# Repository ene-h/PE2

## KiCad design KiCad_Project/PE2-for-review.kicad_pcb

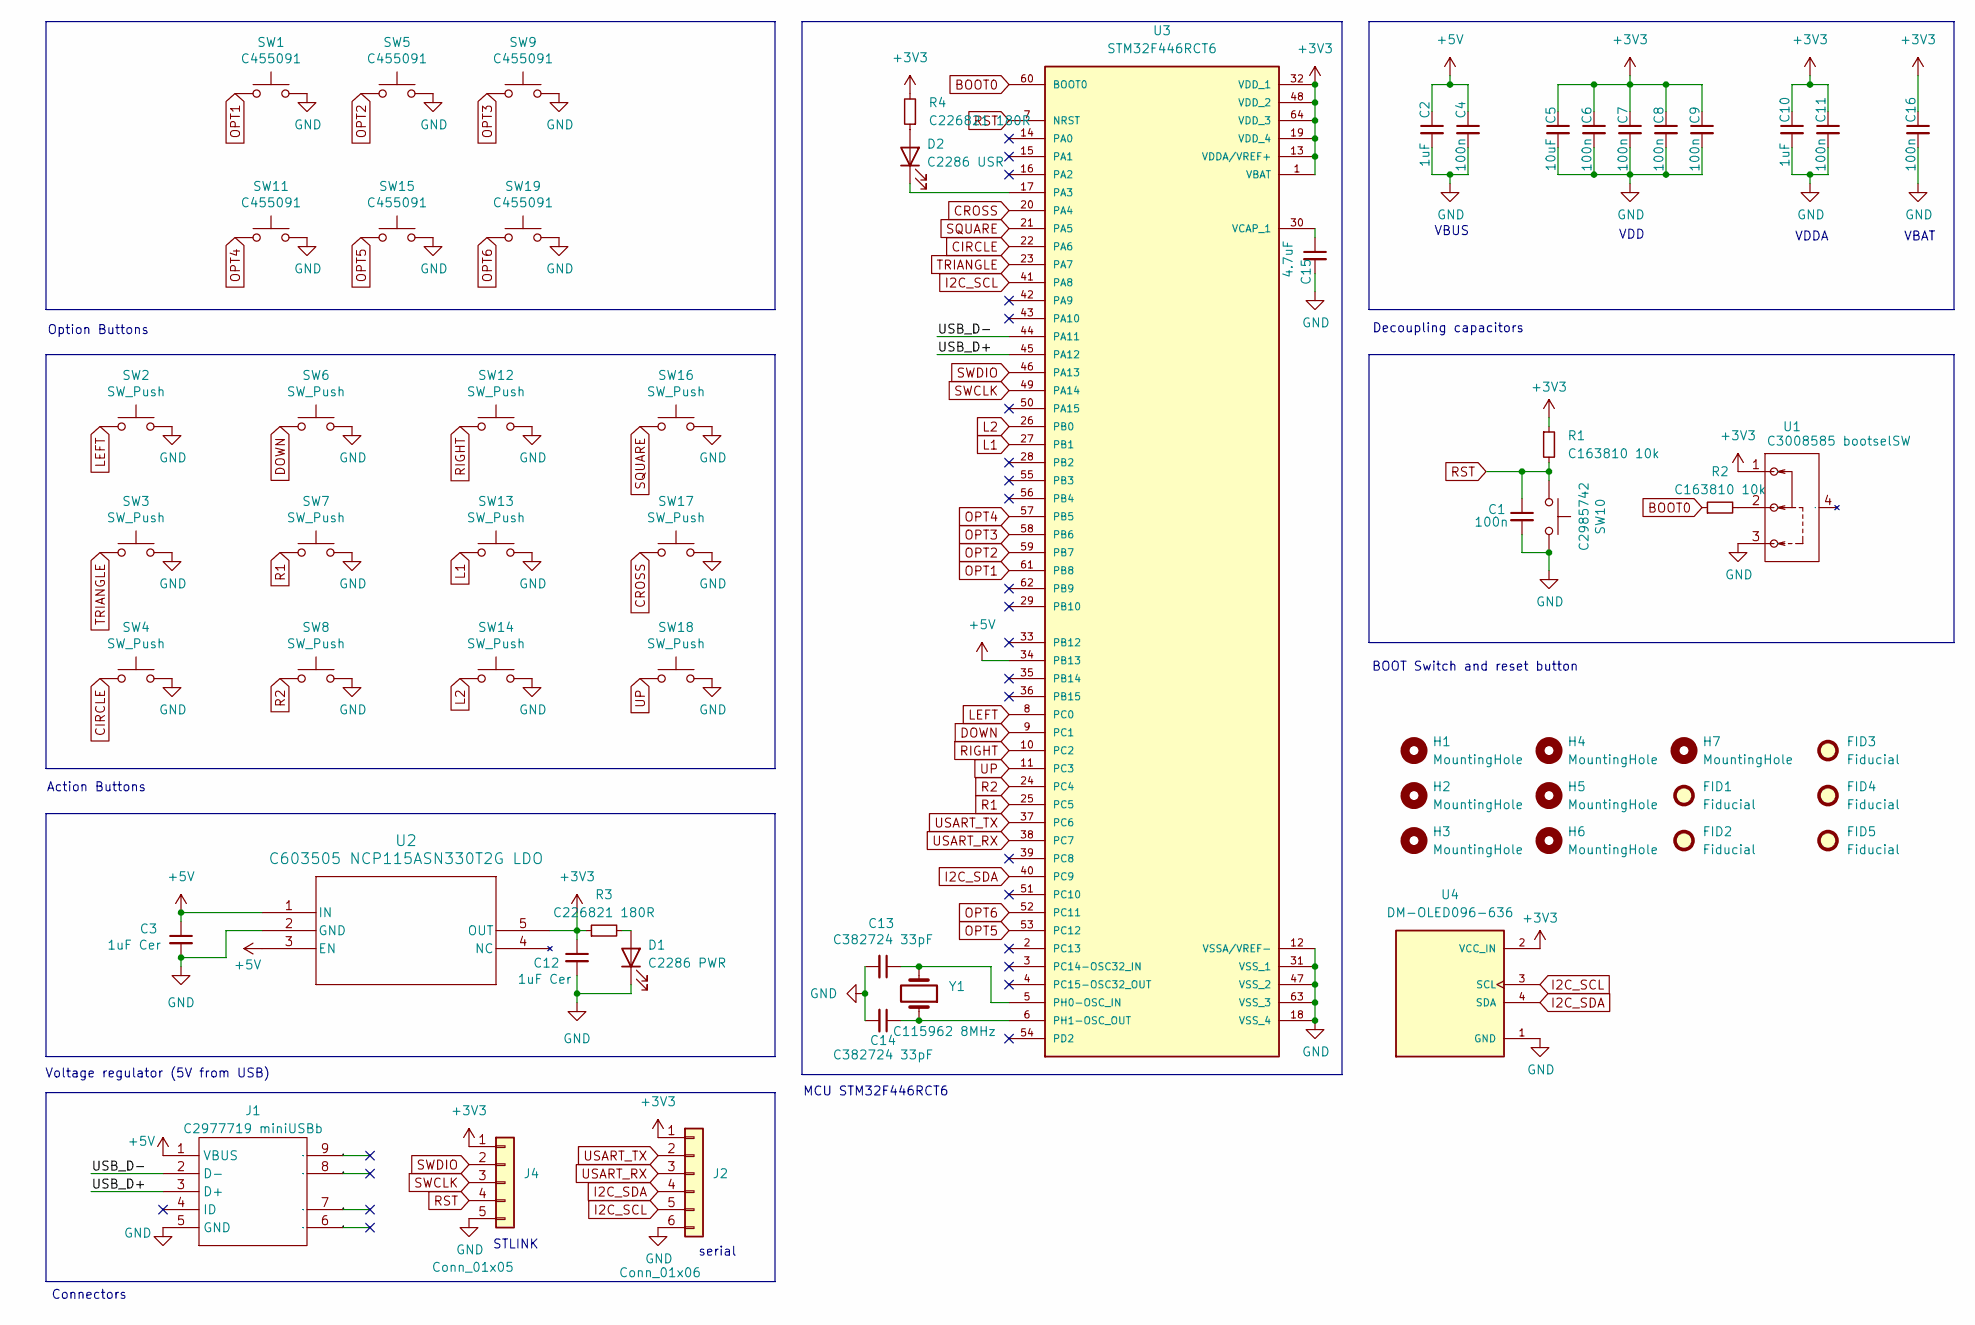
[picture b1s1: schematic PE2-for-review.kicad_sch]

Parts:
C1, C4, C6, C7, C8, C9, C11, C16: 100n; C_0402_1005Metric
C2, C10: 1uF; C_0603_1608Metric
C3, C12: 1uF Cer; C_0603_1608Metric
C5: 10uF; C_0603_1608Metric
C13, C14: C382724 33pF; C_0402_1005Metric
C15: 4.7uF; C_0603_1608Metric
D1: C2286 PWR; LED_0603_1608Metric
D2: C2286 USR; LED_0603_1608Metric
FID1, FID2, FID3: Fiducial; Fiducial_0.75mm_Mask2.25mm
FID4, FID5: Fiducial; Fiducial_0.5mm_Mask1mm
H1, H2, H3, H4, H5, H6, H7: MountingHole; MountingHole_6.3mm
J1: C2977719 miniUSBb; JLC_MINI-USB-SMD
J2: Conn_01x06; PinHeader_1x06_P2.54mm_Horizontal
J4: Conn_01x05; PinHeader_1x05_P2.54mm_Horizontal
R1, R2: C163810 10k; R_0402_1005Metric
R3, R4: C226821 180R; R_0402_1005Metric
SW1, SW5, SW9, SW11, SW15, SW19: C455091; SW_PUSH_6mm_H5mm
SW2, SW3, SW4, SW6, SW7, SW8, SW12, SW13, SW14, SW16, SW17, SW18: SW_Push; Kailh_socket_PG1350_optional
SW10: C2985742; JLC_TactSW_Low-profile
U1: C3008585 bootselSW; JLC_SW-SMD
U2: C603505 NCP115ASN330T2G LDO; SOT95P275X110-5N
U3: STM32F446RCT6
U4: DM-OLED096-636; MODULE_DM-OLED096-636; PARTREV 2018-09-10
Y1: C115962 8MHz; Crystal_SMD_5032-2Pin_5.0x3.2mm

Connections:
+3V3: C5.1, C6.1, C7.1, C8.1, C9.1, C10.1, C11.1, C12.1, C16.1, J2.1, J4.1, R1.1, R3.1, R4.2, U1.1, U2.5 (OUT), U3.1 (VBAT), U3.13 (VDDA/VREF+), U3.19 (VDD_4), U3.32 (VDD_1), U3.48 (VDD_2), U3.64 (VDD_3), U4.2 (VCC_IN)
+5V: C2.1, C3.1, C4.1, J1.1 (VBUS), U2.1 (IN), U2.3 (EN), U3.34 (PB13)
/UC1: J1.9 (EH)
/UC2: J1.8 (EH)
/UC3: J1.7 (EH)
/UC4: J1.6 (EH)
/USB_D+: J1.3 (D+), U3.45 (PA12)
/USB_D-: J1.2 (D-), U3.44 (PA11)
BOOT0: R2.1, U3.60 (BOOT0)
CIRCLE: SW4.1, U3.22 (PA6)
CROSS: SW17.1, U3.20 (PA4)
DOWN: SW6.1, U3.9 (PC1)
GND: C1.2, C2.2, C3.2, C4.2, C5.2, C6.2, C7.2, C8.2, C9.2, C10.2, C11.2, C12.2, C13.2, C14.2, C15.2, C16.2, D1.1 (K), J1.5 (GND), J2.6, J4.5, SW1.2, SW2.2, SW3.2, SW4.2, SW5.2, SW6.2, SW7.2, SW8.2, SW9.2, SW10.2, SW11.2, SW12.2, SW13.2, SW14.2, SW15.2, SW16.2, SW17.2, SW18.2, SW19.2, U1.3, U2.2 (GND), U3.12 (VSSA/VREF-), U3.18 (VSS_4), U3.31 (VSS_1), U3.47 (VSS_2), U3.63 (VSS_3), U4.1 (GND)
I2C_SCL: J2.5, U3.41 (PA8), U4.3 (SCL)
I2C_SDA: J2.4, U3.40 (PC9), U4.4 (SDA)
L1: SW13.1, U3.27 (PB1)
L2: SW14.1, U3.26 (PB0)
LEFT: SW2.1, U3.8 (PC0)
unnamed: D1.2 (A), R3.2
unnamed: D2.2 (A), R4.1
unnamed: D2.1 (K), U3.17 (PA3)
unnamed: R2.2, U1.2
unnamed: C13.1, U3.5 (PH0-OSC_IN), Y1.2
unnamed: C14.1, U3.6 (PH1-OSC_OUT), Y1.1
unnamed: C15.1, U3.30 (VCAP_1)
OPT1: SW1.1, U3.61 (PB8)
OPT2: SW5.1, U3.59 (PB7)
OPT3: SW9.1, U3.58 (PB6)
OPT4: SW11.1, U3.57 (PB5)
OPT5: SW15.1, U3.53 (PC12)
OPT6: SW19.1, U3.52 (PC11)
R1: SW7.1, U3.25 (PC5)
R2: SW8.1, U3.24 (PC4)
RIGHT: SW12.1, U3.10 (PC2)
RST: C1.1, J4.4, R1.2, SW10.1, U3.7 (NRST)
SQUARE: SW16.1, U3.21 (PA5)
SWCLK: J4.3, U3.49 (PA14)
SWDIO: J4.2, U3.46 (PA13)
TRIANGLE: SW3.1, U3.23 (PA7)
UP: SW18.1, U3.11 (PC3)
USART_RX: J2.3, U3.38 (PC7)
USART_TX: J2.2, U3.37 (PC6)

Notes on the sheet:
Voltage regulator (5V from USB)
MCU STM32F446RCT6
serial
BOOT Switch and reset button
STLINK
Connectors
VBAT
Decoupling capacitors
Option Buttons
VBUS
VDD
Action Buttons
VDDA

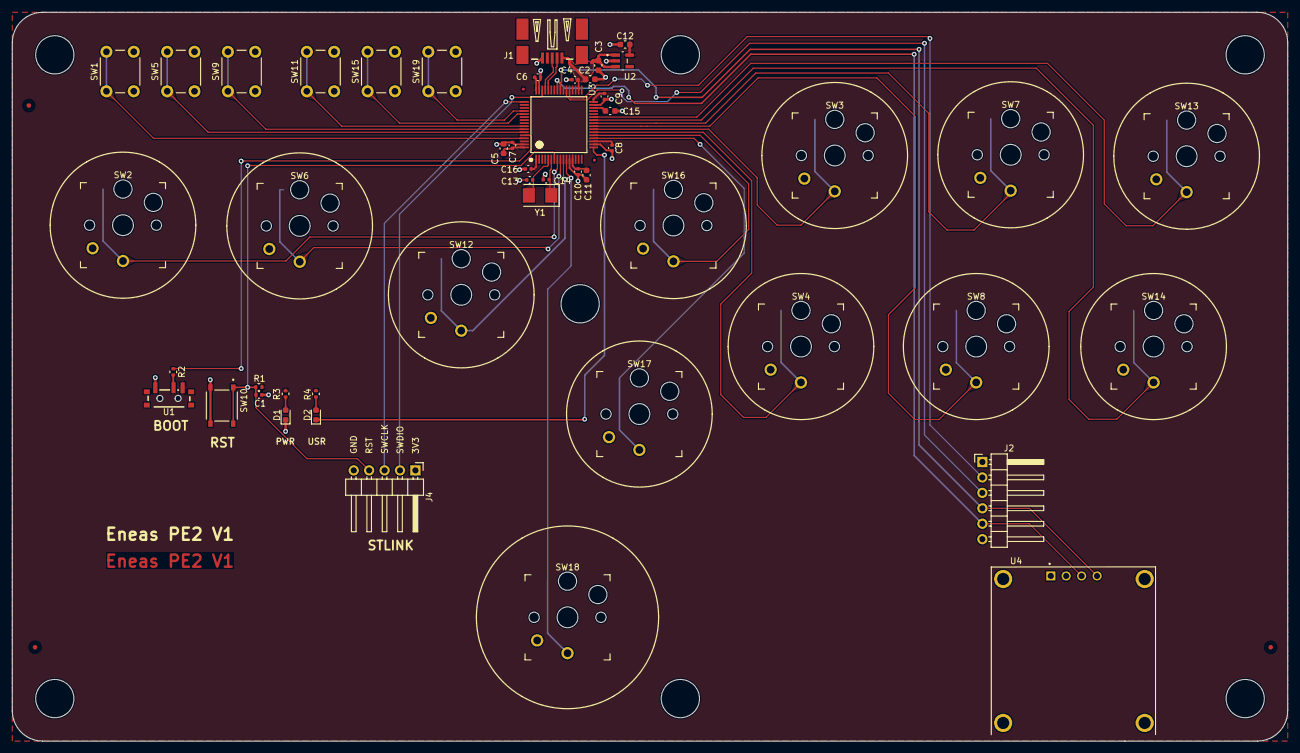
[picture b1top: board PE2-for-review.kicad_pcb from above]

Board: 2 copper layers, 210.0 x 120.0 mm, 61 parts (0 on the bottom side), 38 nets.

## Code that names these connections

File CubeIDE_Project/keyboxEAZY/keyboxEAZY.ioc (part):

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Mcu.Name=STM32F446R(C-E)Tx
Mcu.Package=LQFP64
Mcu.UserName=STM32F446RCTx
PA11.Mode=Device_Only
PA11.Signal=USB_OTG_FS_DM
PA12.Mode=Device_Only
PA12.Signal=USB_OTG_FS_DP
PA13.Signal=SYS_JTMS-SWDIO
PA3.GPIOParameters=GPIO_Label
PA3.GPIO_Label=LED
PA3.Signal=GPIO_Output
PA4.GPIOParameters=GPIO_PuPd,GPIO_Label,GPIO_Mode
PA4.GPIO_Label=LK
PA4.GPIO_Mode=GPIO_MODE_INPUT
PA4.GPIO_PuPd=GPIO_PULLUP
PA4.Signal=GPIO_Input
PA5.GPIOParameters=GPIO_PuPd,GPIO_Label,GPIO_Mode
PA5.GPIO_Label=LP
PA5.GPIO_Mode=GPIO_MODE_INPUT
PA5.GPIO_PuPd=GPIO_PULLUP
PA5.Signal=GPIO_Input
PA6.GPIOParameters=GPIO_PuPd,GPIO_Label,GPIO_Mode
PA6.GPIO_Label=MK
PA6.GPIO_Mode=GPIO_MODE_INPUT
PA6.GPIO_PuPd=GPIO_PULLUP
PA6.Signal=GPIO_Input
PA7.GPIOParameters=GPIO_PuPd,GPIO_Label,GPIO_Mode
PA7.GPIO_Label=MP
PA7.GPIO_Mode=GPIO_MODE_INPUT
PA7.GPIO_PuPd=GPIO_PULLUP
PA7.Signal=GPIO_Input
PA8.GPIOParameters=GPIO_Pu
PA8.GPIO_Pu=GPIO_PULLUP
PA8.Mode=I2C
PA8.Signal=I2C3_SCL
PB0.GPIOParameters=GPIO_PuPd,GPIO_Label
PB0.GPIO_Label=EXK
PB0.GPIO_PuPd=GPIO_PULLUP
PB0.Signal=GPIO_Input
PB1.GPIOParameters=GPIO_PuPd,GPIO_Label
PB1.GPIO_Label=EXP
PB1.GPIO_PuPd=GPIO_PULLUP
PB1.Signal=GPIO_Input
PB13.Signal=USB_OTG_HS_VBUS
PB5.GPIOParameters=GPIO_PuPd,GPIO_Label
PB5.GPIO_Label=OPT4
PB5.GPIO_PuPd=GPIO_PULLUP
PB5.Signal=GPIO_Input
PB6.GPIOParameters=GPIO_PuPd,GPIO_Label
PB6.GPIO_Label=OPT3
PB6.GPIO_PuPd=GPIO_PULLUP
PB6.Signal=GPIO_Input
PB7.GPIOParameters=GPIO_PuPd,GPIO_Label
PB7.GPIO_Label=OPT2
PB7.GPIO_PuPd=GPIO_PULLUP
PB7.Signal=GPIO_Input
PB8.GPIOParameters=GPIO_PuPd,GPIO_Label
PB8.GPIO_Label=OPT1
PB8.GPIO_PuPd=GPIO_PULLUP
PB8.Signal=GPIO_Input
PC0.GPIOParameters=GPIO_PuPd,GPIO_Label,GPIO_Mode
PC0.GPIO_Label=LEFT
PC0.GPIO_Mode=GPIO_MODE_INPUT
PC0.GPIO_PuPd=GPIO_PULLUP
PC0.Signal=GPIO_Input
PC1.GPIOParameters=GPIO_PuPd,GPIO_Label,GPIO_Mode
PC1.GPIO_Label=DOWN
PC1.GPIO_Mode=GPIO_MODE_INPUT
PC1.GPIO_PuPd=GPIO_PULLUP
PC1.Signal=GPIO_Input
PC11.GPIOParameters=GPIO_PuPd,GPIO_Label
PC11.GPIO_Label=OPT6
PC11.GPIO_PuPd=GPIO_PULLUP
PC11.Signal=GPIO_Input
PC12.GPIOParameters=GPIO_PuPd,GPIO_Label
PC12.GPIO_Label=OPT5
PC12.GPIO_PuPd=GPIO_PULLUP
PC12.Signal=GPIO_Input
PC2.GPIOParameters=GPIO_PuPd,GPIO_Label,GPIO_Mode
PC2.GPIO_Label=RIGHT
PC2.GPIO_Mode=GPIO_MODE_INPUT
PC2.GPIO_PuPd=GPIO_PULLUP
PC2.Signal=GPIO_Input
PC3.GPIOParameters=GPIO_PuPd,GPIO_Label,GPIO_Mode
PC3.GPIO_Label=UP
PC3.GPIO_Mode=GPIO_MODE_INPUT
PC3.GPIO_PuPd=GPIO_PULLUP
PC3.Signal=GPIO_Input
PC4.GPIOParameters=GPIO_PuPd,GPIO_Label
PC4.GPIO_Label=HK
PC4.GPIO_PuPd=GPIO_PULLUP
PC4.Signal=GPIO_Input
PC5.GPIOParameters=GPIO_PuPd,GPIO_Label
PC5.GPIO_Label=HP
PC5.GPIO_PuPd=GPIO_PULLUP
PC5.Signal=GPIO_Input
PC6.Mode=Asynchronous
PC6.Signal=USART6_TX
PC7.Mode=Asynchronous
PC7.Signal=USART6_RX
PC9.GPIOParameters=GPIO_Pu
PC9.GPIO_Pu=GPIO_PULLUP
PC9.Mode=I2C
PC9.Signal=I2C3_SDA
PH0-OSC_IN.Mode=HSE-External-Oscillator
PH0-OSC_IN.Signal=RCC_OSC_IN
PH1-OSC_OUT.Mode=HSE-External-Oscillator
PH1-OSC_OUT.Signal=RCC_OSC_OUT
RCC.HSE_VALUE=8000000
RCC.SYSCLKFreq_VALUE=144000000
RCC.SYSCLKSource=RCC_SYSCLKSOURCE_PLLRCLK
board=custom

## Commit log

2024-06-01 KiCad and CubeIDE Project added
2024-06-01 3D files for case added
2024-06-01 Production files added
2024-06-01 Demo video added
2024-06-01 Windows cfg demo video added
2024-06-01 updated comments in main + corrected I2C rate to actual value used on silicon
2024-06-01 prettified schematic slightly + added schematic pdf
2024-06-01 added schematic and PCB PDFs
2024-06-01 added datasheets
2024-06-01 added datasheet
2024-06-01 added verslag
